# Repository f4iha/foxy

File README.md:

# Foxy, a radio beacon based on SI5351

Based on the SI5351 clock generator, this is a simple VHF beacon with the target to be used for "Fox hunt". It explains its name : foxy.

To know more about the projet : [the article in french](https://www.f4iha.fr/2024/12/04/foxy-un-module-de-chasse-au-renard-pour-quelques-euros/)

## Hardware

The harware is based on an Arduino Nano, a SI5351 and a filter based on LC components.
The Kicad project (schema and PCB) are available in the electronics folder. Fabrication files are available in the electronics/foxy/Gerber folder.

## Software

Very simple software here which relying on the SI5351 library from https://github.com/etherkit/Si5351Arduino
The code can be built and deployed with platform.io

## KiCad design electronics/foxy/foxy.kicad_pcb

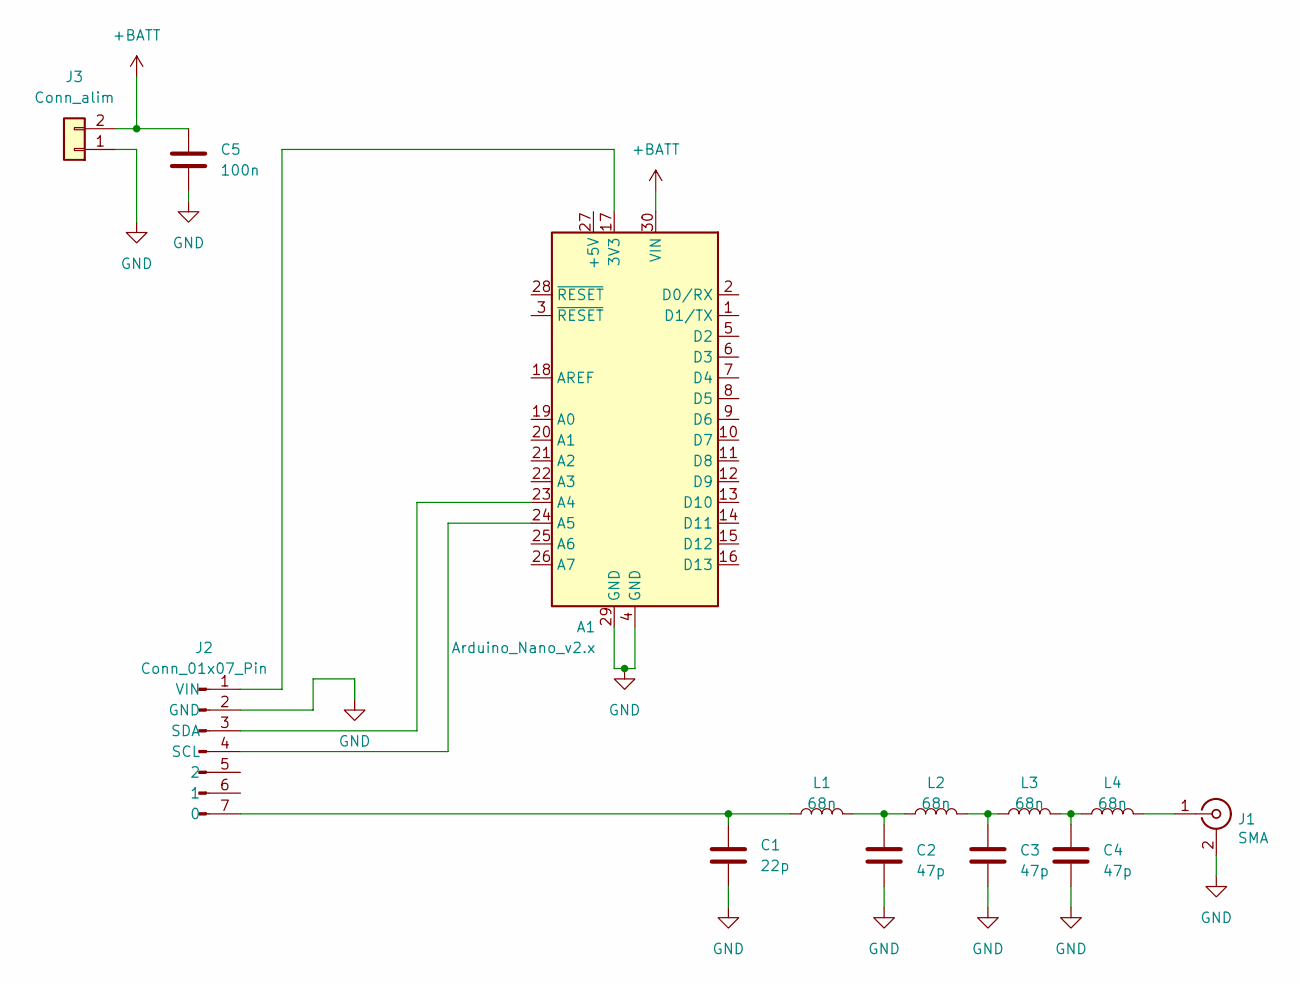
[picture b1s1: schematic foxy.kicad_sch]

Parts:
A1: Arduino_Nano_v2.x; Arduino_Nano
C1: 22p; C_0805_2012Metric
C2, C3, C4: 47p; C_0805_2012Metric
C5: 100n; C_0805_2012Metric_Pad1.18x1.45mm_HandSolder
J1: SMA; SMA_EDGE_NRW
J2: Conn_01x07_Pin; PinHeader_1x07_P2.54mm_Vertical
J3: Conn_alim; JST_XH_B2B-XH-A_1x02_P2.50mm_Vertical
L1, L2, L3, L4: 68n; L_Coilcraft_1812SMS

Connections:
+BATT: A1.30 (VIN), C5.1, J3.2
GND: A1.4 (GND), A1.29 (GND), C1.2, C2.2, C3.2, C4.2, C5.2, J1.2 (Ext), J2.2 (GND), J3.1
unnamed: A1.17 (3V3), J2.1 (VIN)
unnamed: A1.23 (A4), J2.3 (SDA)
unnamed: A1.24 (A5), J2.4 (SCL)
unnamed: C2.1, L1.2, L2.1
unnamed: C3.1, L2.2, L3.1
unnamed: C4.1, L3.2, L4.1
unnamed: J1.1 (In), L4.2
unnamed: C1.1, J2.7 (0), L1.1

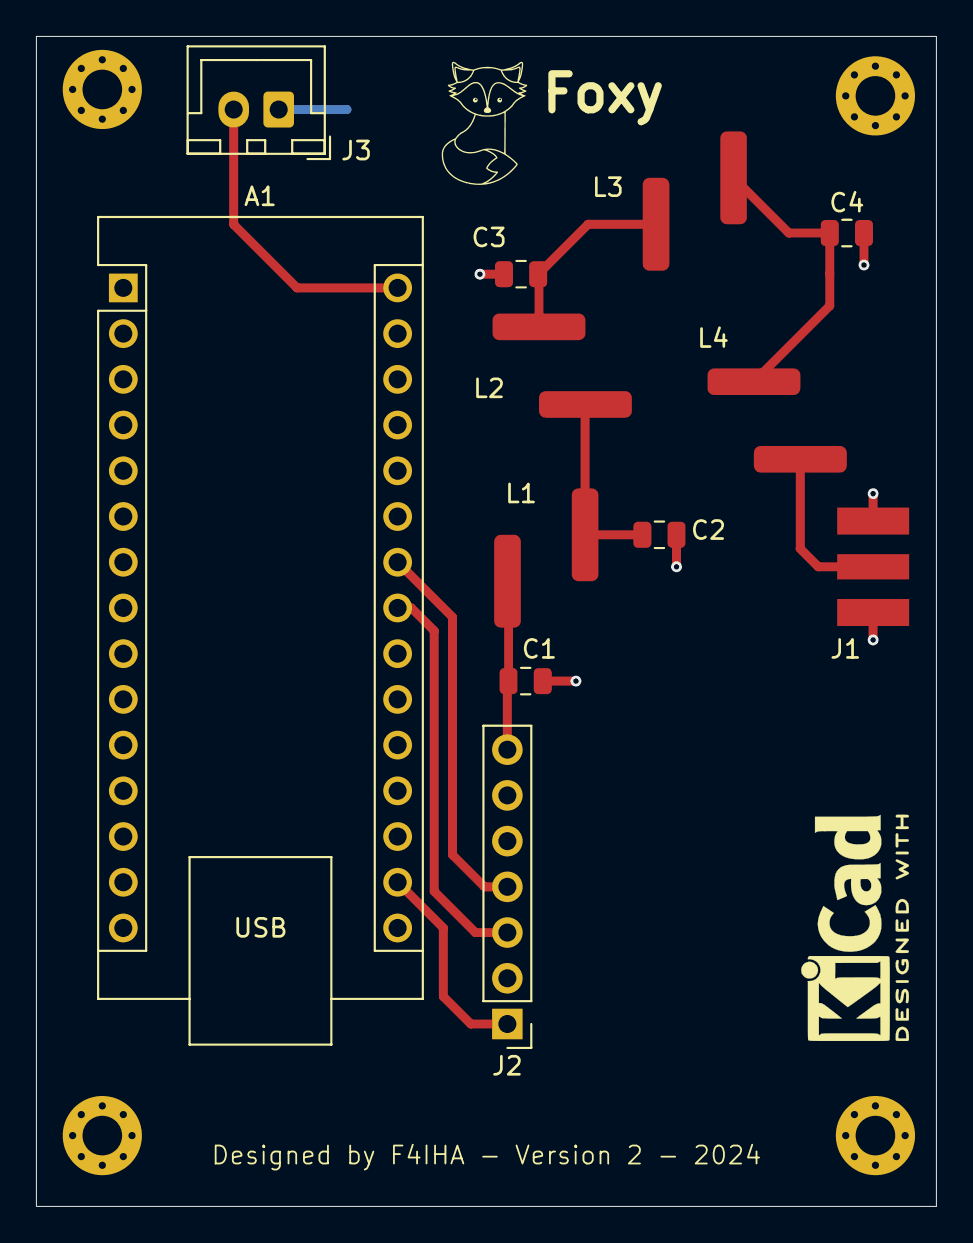
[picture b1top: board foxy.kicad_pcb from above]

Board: 2 copper layers, 50.0 x 65.0 mm, 13 parts (1 on the bottom side), 10 nets.

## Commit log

2024-10-20 Initial project commit
2024-10-20 Add README
2024-12-04 add function blocs in schema
2024-12-04 Add link to french article
